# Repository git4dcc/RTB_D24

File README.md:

# RTB_D24

My Homebrew D24 is a single-sided DIY mobile decoder featuring a NEM-651 connector. While it shares the exact same dimensions as the [D16](https://github.com/git4dcc/RTB_D16), it offers additional AUX channels and supports WS28xx LED connections. It is fully designed for integration into the RTB digital control ecosystem.

<details>
<summary>See also</summary>

- [RTB_D16 - NEM651](/../../../../git4dcc/RTB_D16)
- [RTB_D20 - NEM651](/../../../../git4dcc/RTB_D20)
- [RTB_D21 - Next18](/../../../../git4dcc/RTB_D21)
- [RTB_D22 - Plux16](/../../../../git4dcc/RTB_D22)
- [RTB_D23 - NEM652](/../../../../git4dcc/RTB_D23)

</details>

<details>
<summary>User Guides</summary>

- User Guide - DE
- [User Guide - EN](https://rtb4dcc.de/rtb_decoder_reference_en/)

</details>

<br>

The decoder has the following features,
- **NEM-651** connector
- **DCC**
  - DCC-A automatic logon
  - DCC-R protocol extension
  - Service Mode Programming
- **Railcom**
  - Channel 1/2
  - POM, xPOM
  - DYN: Speed, QoS, Track-voltage, Motor-current, AUX-current, Temp, Distance travelled
- Single sided
- Dimension: 17 x 11 mm
- 7-20V track voltage
- heartbeat LED
- adjustable max motor current (default 300mA)
- adjustable max AUX current (default 500mA)
- over temp protection
- Function output: LV/LR/AUX1/AUX2 (dimmable, 1.4kHz) open drain
- Function output: AUX3/AUX4/AUX5/AUX6/AUX7 logic level (5V)
  - AUX3/AUX4 can be configured to drive WS28xx chips
- optional external buffer capacitor (max. 1500uF)
- <10mA idle power consumption
- Firmware update over main tracks via DCC-R protocol

# Hardware
The current PCB layout uses SMD footprints with 0.5mm pitch and mainly 0402 parts. Reflow soldering is recommended, handsoldering will be difficult.

**Note:** The '5V zone' silk text can be misleading as the above test point is **not** 5V source but rather the UPDI interface.

## PCB
- 6-layer PCB, FR4, 17 x 11 x 0.8mm (single sided)
- CPU: AVR64DA32
- Motor bridge: DRV8231
- Connector: NEM-651

## Kicad
[Schematic](doc/D24_schematic.pdf) | [Layout](doc/D24_layout.pdf) | [Gerber](gerber)

<details>
<summary>Dependency</summary>
<br>

:yellow_circle: Requires my Kicad project library [RTB_SamacSys](https://github.com/git4dcc/RTB_SamacSys) in the same directory tree.

</details>

## Firmware
Filename structure: { **pcb** }{ **code** }{ **version** }.hex

Example: **D16F0001**.hex

|   | Description |
| --- | --- |
| **pcb** | Name of matching hardware (**D24**) |
| **code** | Type of code contained (**R**=rom, **B**=bootloader, **F**=flash, **U**=bld update, **P**=UPDI factory code) |
| **version** | Release version (**####**) |

[Firmware files](firmware)

# Images
| top | bottom |
| --- | --- |
|  |  |

# YouTube
Some YouTubes to see the D24 decoder in action.<br><br>

This project is intended for hobby use only and is distributed in accordance with the Apache License 2.0 agreement.

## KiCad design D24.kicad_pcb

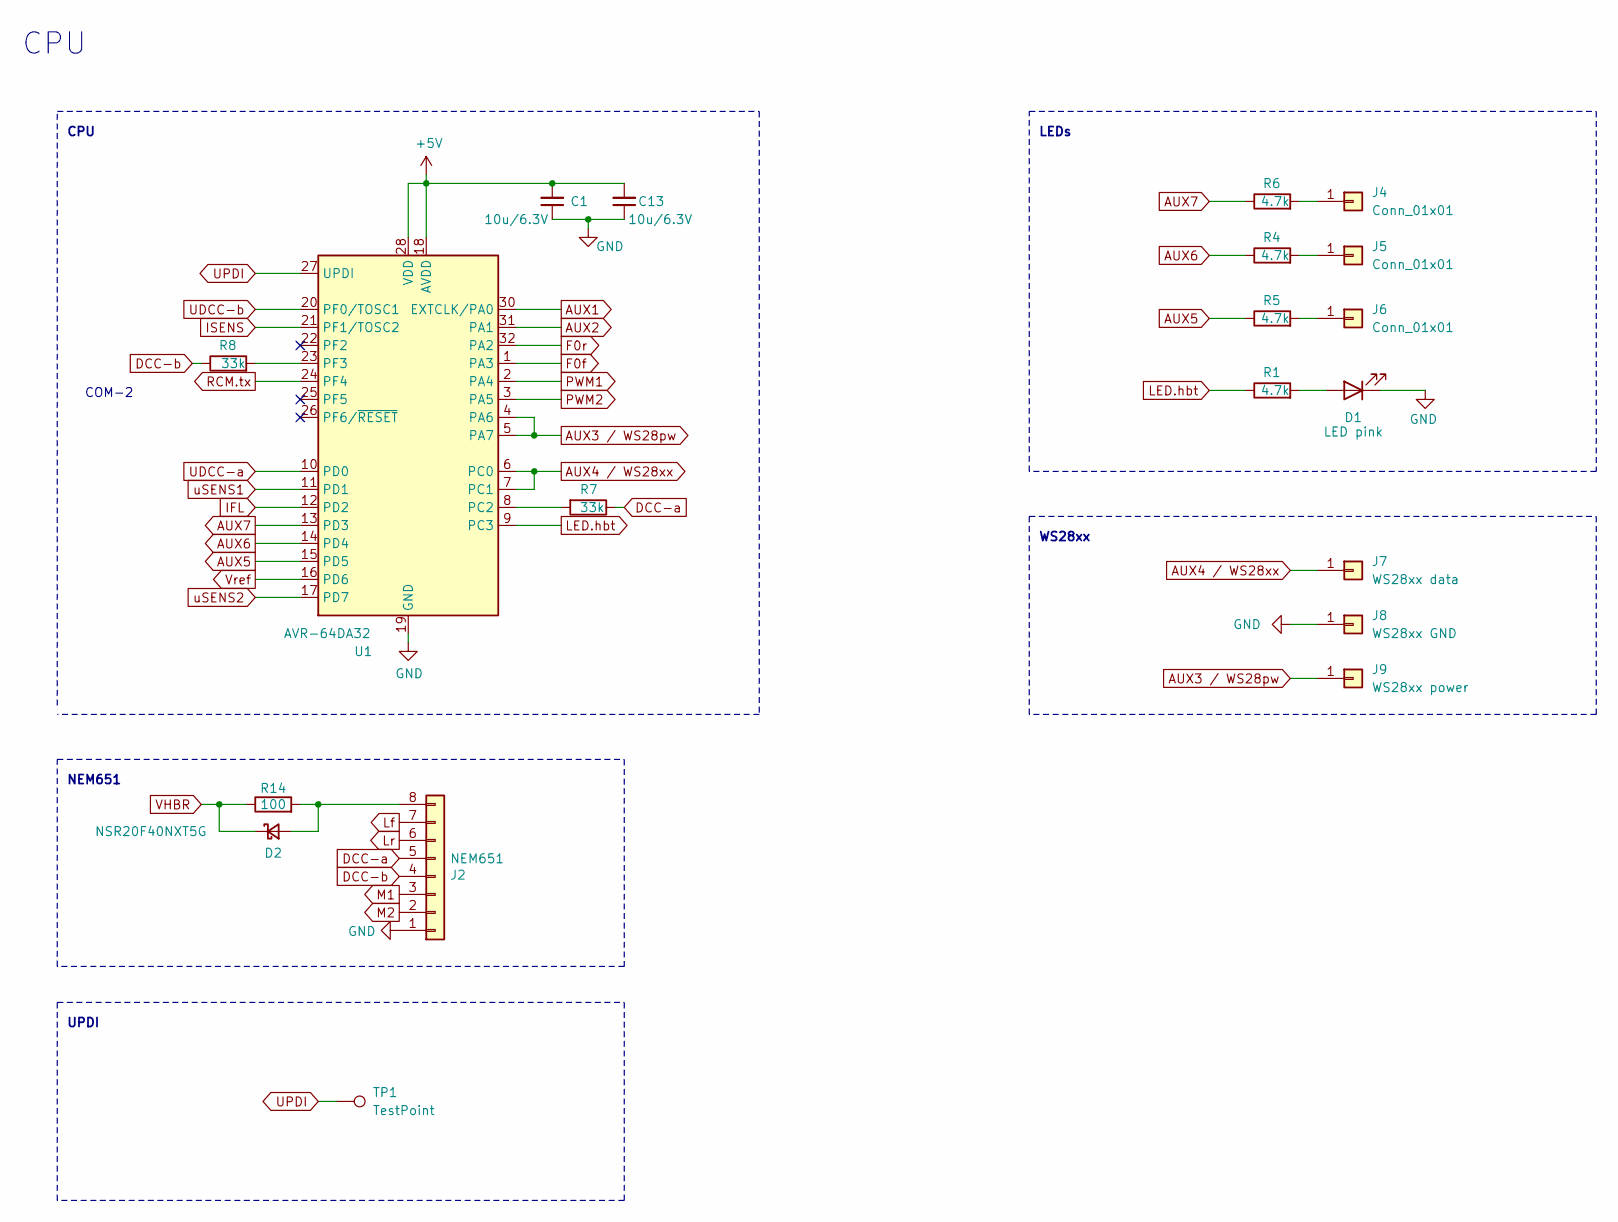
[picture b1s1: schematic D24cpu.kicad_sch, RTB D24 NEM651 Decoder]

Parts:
C1, C13: 10u/6.3V; C_0402_1005Metric; LCSC Part # C15525
D1: LED pink; LED_0402_1005Metric
D2: NSR20F40NXT5G; LCSC Part # C153761
J2: NEM651; PinHeader_1x08_P1.27mm_Horizontal
J4, J5, J6: Conn_01x01; Solder_Pad_1.0x1.0mm
J7: WS28xx data; Solder_Pad_1.0x1.0mm
J8: WS28xx GND; Solder_Pad_1.0x1.0mm
J9: WS28xx power; Solder_Pad_1.0x1.0mm
R1, R4, R5, R6: 4.7k; R_0402_1005Metric; LCSC Part # C25900
R7, R8: 33k; R_0402_1005Metric; LCSC Part # C25779
R14: 100; R_0603_1608Metric; LCSC Part # C22775
TP1: TestPoint; TestPoint_Pad_D1.0mm
U1: AVR-64DA32; VQFN-32-1EP_5x5mm_P0.5mm_EP3.1x3.1mm; LCSC Part # C3225673

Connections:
+5V: C1.2, C13.2, U1.18 (AVDD), U1.28 (VDD); also elsewhere on the board
AUX1: U1.30 (EXTCLK/PA0); also elsewhere on the board
AUX2: U1.31 (PA1); also elsewhere on the board
AUX3 / WS28pw: J9.1 (Pin_1_1), U1.4 (PA6), U1.5 (PA7)
AUX4 / WS28xx: J7.1 (Pin_1_1), U1.6 (PC0), U1.7 (PC1)
AUX5: R5.1, U1.15 (PD5)
AUX6: R4.1, U1.14 (PD4)
AUX7: R6.1, U1.13 (PD3)
DCC-a: J2.5, R7.1; also elsewhere on the board
DCC-b: J2.4, R8.1; also elsewhere on the board
F0f: U1.1 (PA3); also elsewhere on the board
F0r: U1.32 (PA2); also elsewhere on the board
GND: C1.1, C13.1, D1.1 (K), J2.1, J8.1 (Pin_1_1), U1.19 (GND), U1.29 (GND), U1.33 (GND); also elsewhere on the board
IFL: U1.12 (PD2); also elsewhere on the board
ISENS: U1.21 (PF1/TOSC2); also elsewhere on the board
LED.hbt: R1.1, U1.9 (PC3)
Lf: J2.7; also elsewhere on the board
Lr: J2.6; also elsewhere on the board
M1: J2.3; also elsewhere on the board
M2: J2.2; also elsewhere on the board
unnamed: D1.2 (A), R1.2
unnamed: D2.2 (A), J2.8, R14.2
unnamed: J4.1 (Pin_1_1), R6.2
unnamed: J5.1 (Pin_1_1), R4.2
unnamed: J6.1 (Pin_1_1), R5.2
unnamed: R7.2, U1.8 (PC2)
unnamed: R8.2, U1.23 (PF3)
PWM1: U1.2 (PA4); also elsewhere on the board
PWM2: U1.3 (PA5); also elsewhere on the board
RCM.tx: U1.24 (PF4); also elsewhere on the board
UDCC-a: U1.10 (PD0); also elsewhere on the board
UDCC-b: U1.20 (PF0/TOSC1); also elsewhere on the board
UPDI: TP1.1 (1_1), U1.27 (UPDI)
VHBR: D2.1 (K), R14.1; also elsewhere on the board
Vref: U1.16 (PD6); also elsewhere on the board
uSENS1: U1.11 (PD1); also elsewhere on the board
uSENS2: U1.17 (PD7); also elsewhere on the board

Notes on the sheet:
CPU
WS28xx
NEM651
LEDs
UPDI
COM-2

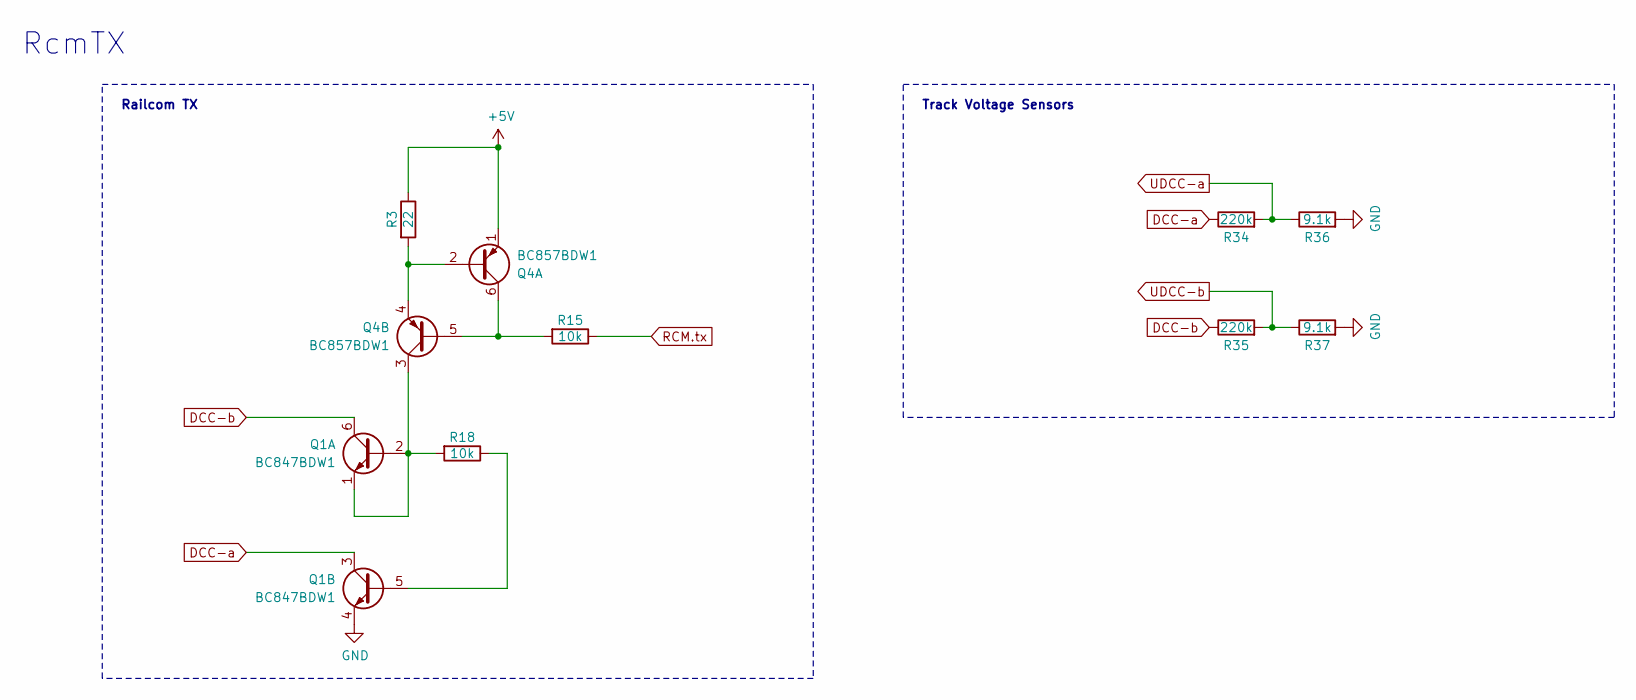
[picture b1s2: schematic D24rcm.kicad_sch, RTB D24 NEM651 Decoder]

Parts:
Q1: BC847BDW1; SOT-666; LCSC Part # C455062
Q4: BC857BDW1; SOT-666; LCSC Part # C282521
R3: 22; R_0402_1005Metric; LCSC Part # C25092
R15, R18: 10k; R_0402_1005Metric; LCSC Part # C25744
R34, R35: 220k; R_0402_1005Metric; LCSC Part # C25767
R36, R37: 9.1k; R_0402_1005Metric; LCSC Part # C25926

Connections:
+5V: Q4.1 (E1), R3.1; also elsewhere on the board
DCC-a: Q1.3 (C2), R34.1; also elsewhere on the board
DCC-b: Q1.6 (C1), R35.1; also elsewhere on the board
GND: Q1.4 (E2), R36.2, R37.2; also elsewhere on the board
unnamed: Q1.1 (E1), Q1.2 (B1), Q4.3 (C2), R18.2
unnamed: Q1.5 (B2), R18.1
unnamed: Q4.2 (B1), Q4.4 (E2), R3.2
unnamed: Q4.5 (B2), Q4.6 (C1), R15.2
RCM.tx: R15.1; also elsewhere on the board
UDCC-a: R34.2, R36.1; also elsewhere on the board
UDCC-b: R35.2, R37.1; also elsewhere on the board

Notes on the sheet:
Railcom TX
RcmTX
Track Voltage Sensors

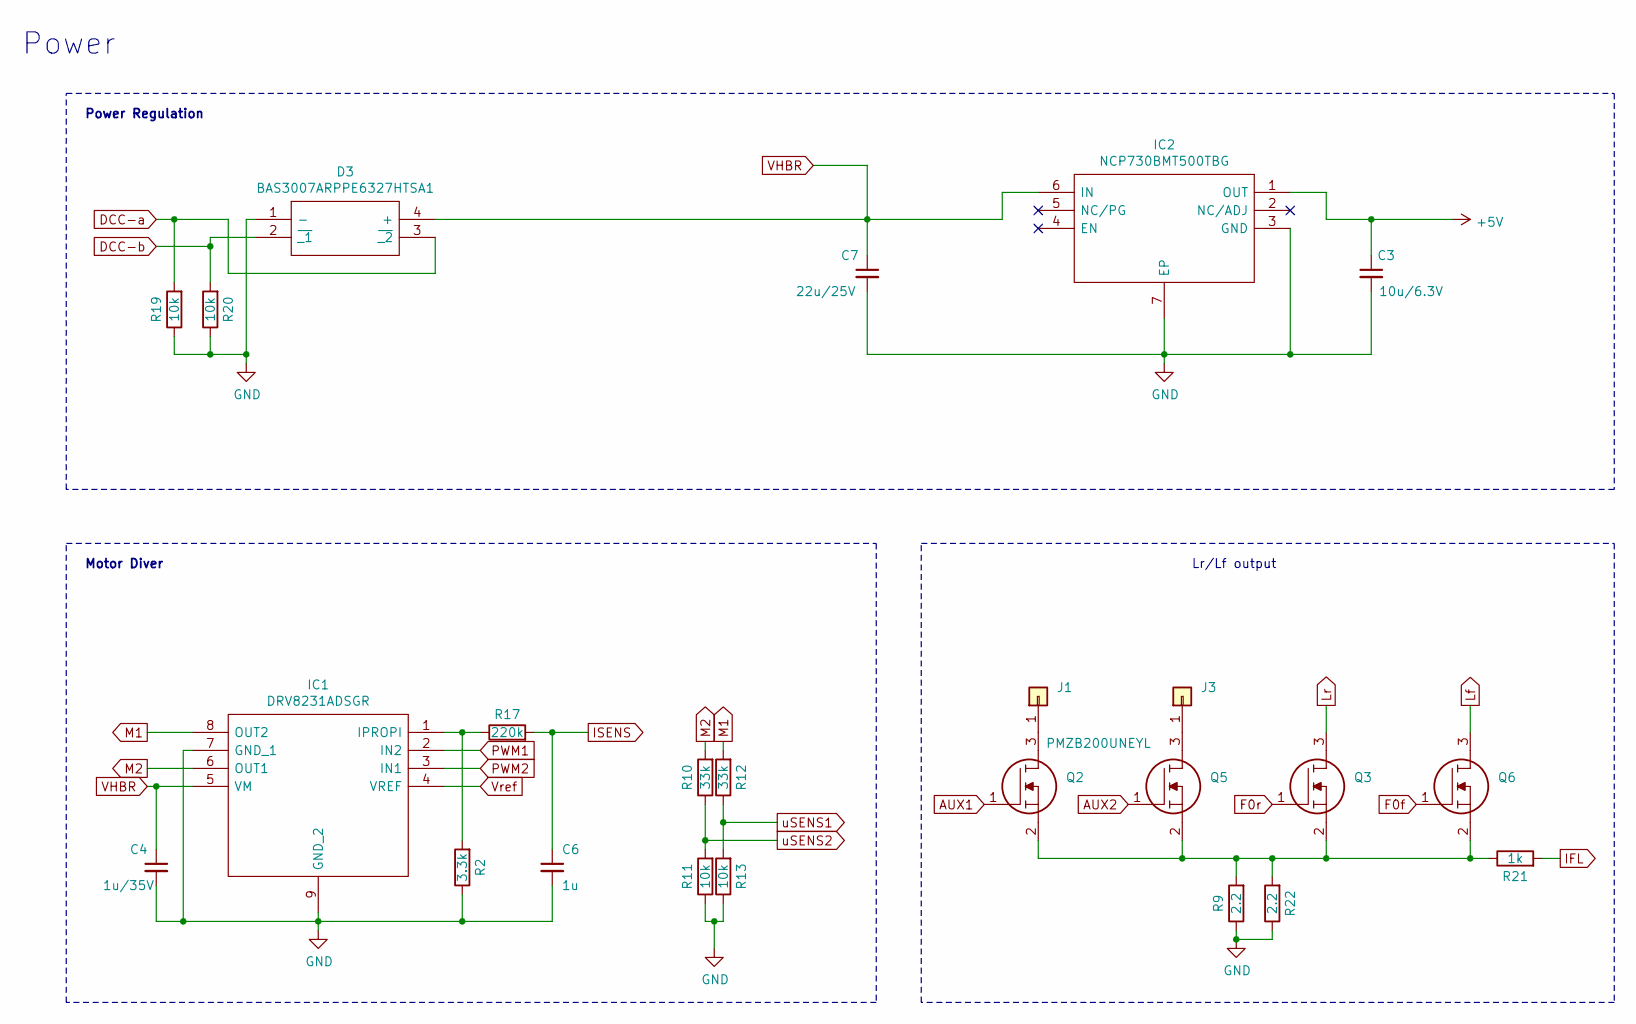
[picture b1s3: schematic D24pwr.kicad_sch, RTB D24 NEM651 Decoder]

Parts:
C3: 10u/6.3V; C_0402_1005Metric; LCSC Part # C15525
C4: 1u/35V; C_0603_1608Metric; LCSC Part # C15849
C6: 1u; C_0402_1005Metric; LCSC Part # C52923
C7: 22u/25V; C_0805_2012Metric; LCSC Part # C45783
D3: BAS3007ARPPE6327HTSA1; BF998215; LCSC Part # C6430958
IC1: DRV8231ADSGR; SON50P200X200X80-9N; LCSC Part # C5139865
IC2: NCP730BMT500TBG; WSON-6-1EP_2x2mm_P0.65mm_EP1x1.6mm_ThermalVias; LCSC Part # C892822
J1, J3: Conn_01x01; Solder_Pad_1.0x1.0mm
Q2, Q3, Q5, Q6: PMZB200UNEYL; LCSC Part # C547292
R2: 3.3k; R_0402_1005Metric; LCSC Part # C25890
R9, R22: 2.2; R_0402_1005Metric; LCSC Part # C2079158
R10, R12: 33k; R_0402_1005Metric; LCSC Part # C25779
R11, R13, R19, R20: 10k; R_0402_1005Metric; LCSC Part # C25744
R17: 220k; R_0402_1005Metric; LCSC Part # C25767
R21: 1k; R_0402_1005Metric; LCSC Part # C11702

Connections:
+5V: C3.1, IC2.1 (OUT); also elsewhere on the board
AUX1: Q2.1; also elsewhere on the board
AUX2: Q5.1; also elsewhere on the board
DCC-a: D3.3 (~_2), R19.2; also elsewhere on the board
DCC-b: D3.2 (~_1), R20.2; also elsewhere on the board
F0f: Q6.1; also elsewhere on the board
F0r: Q3.1; also elsewhere on the board
GND: C3.2, C4.2, C6.2, C7.2, D3.1 (-), IC1.7 (GND_1), IC1.9 (GND_2), IC2.3 (GND), IC2.7 (EP), R2.1, R9.1, R11.1, R13.1, R19.1, R20.1, R22.1; also elsewhere on the board
IFL: R21.2; also elsewhere on the board
ISENS: C6.1, R17.2; also elsewhere on the board
Lf: Q6.3; also elsewhere on the board
Lr: Q3.3; also elsewhere on the board
M1: IC1.8 (OUT2), R12.2; also elsewhere on the board
M2: IC1.6 (OUT1), R10.2; also elsewhere on the board
unnamed: IC1.1 (IPROPI), R2.2, R17.1
unnamed: J1.1 (Pin_1_1), Q2.3
unnamed: J3.1 (Pin_1_1), Q5.3
unnamed: Q2.2, Q3.2, Q5.2, Q6.2, R9.2, R21.1, R22.2
PWM1: IC1.2 (IN2); also elsewhere on the board
PWM2: IC1.3 (IN1); also elsewhere on the board
VHBR: C4.1, C7.1, D3.4 (+), IC1.5 (VM), IC2.6 (IN); also elsewhere on the board
Vref: IC1.4 (VREF); also elsewhere on the board
uSENS1: R12.1, R13.2; also elsewhere on the board
uSENS2: R10.1, R11.2; also elsewhere on the board

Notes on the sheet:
Lr/Lf output
Motor Diver
Power
Power Regulation

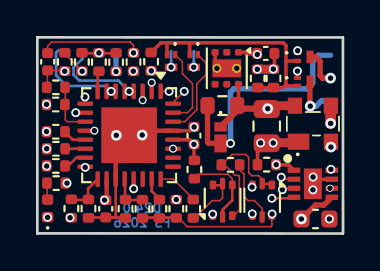
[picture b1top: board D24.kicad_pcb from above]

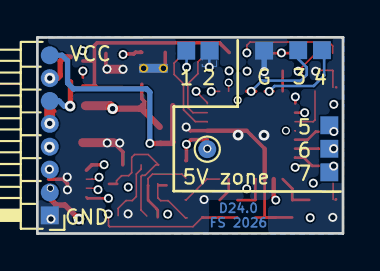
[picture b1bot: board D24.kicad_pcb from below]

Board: 6 copper layers, 17.0 x 10.9 mm, 53 parts (10 on the bottom side), 45 nets.

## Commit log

2026-05-31 initial
2026-06-14 refined BOM
2026-06-14 Update README to remove custom RTB entries
    Removed custom RTB entries from the README.
2026-06-15 git mirror

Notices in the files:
D24.kicad_pcb:
Licensed under the Apache License, Version 2
